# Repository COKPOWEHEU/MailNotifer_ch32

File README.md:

# MailNotifer_ch32
My version of Mail Notifer by RISO KAGAKU

The device that allows you to indicate something using an RGB LED. Also, unlike the prototype, an LCD screen has been added to display text information. Many features are now configured using files on a virtual "flash drive"

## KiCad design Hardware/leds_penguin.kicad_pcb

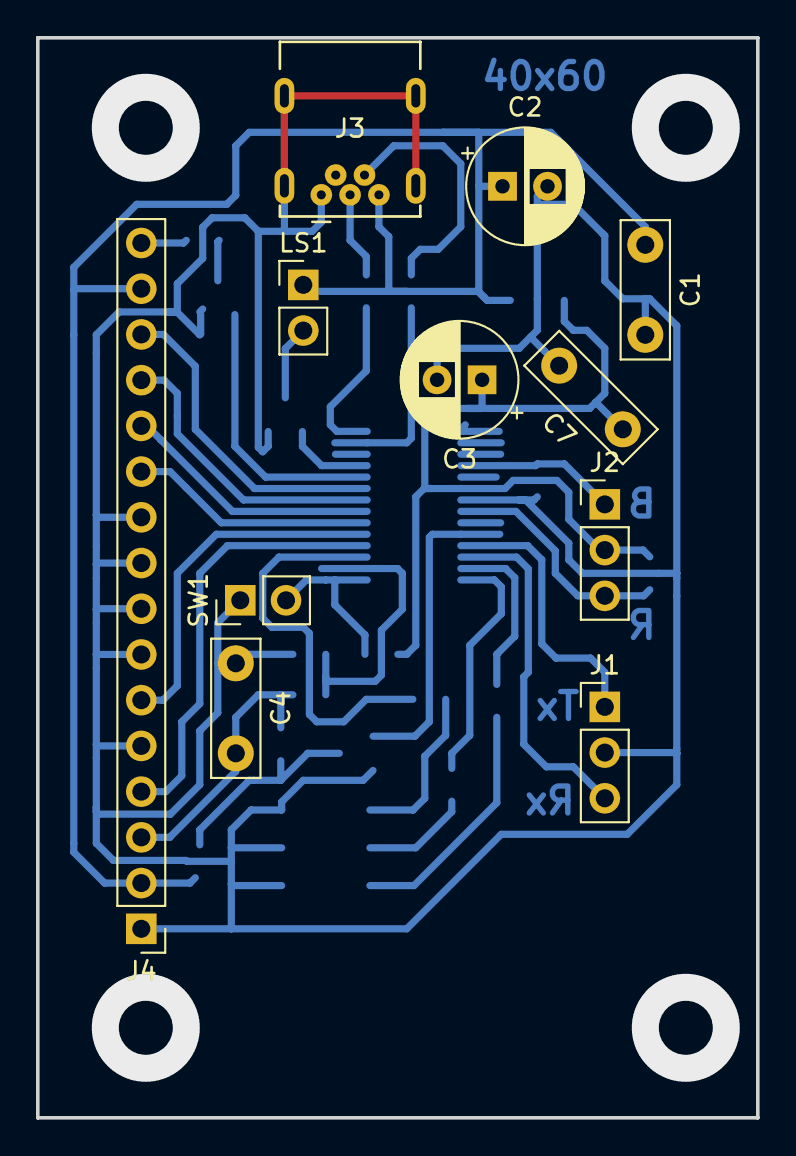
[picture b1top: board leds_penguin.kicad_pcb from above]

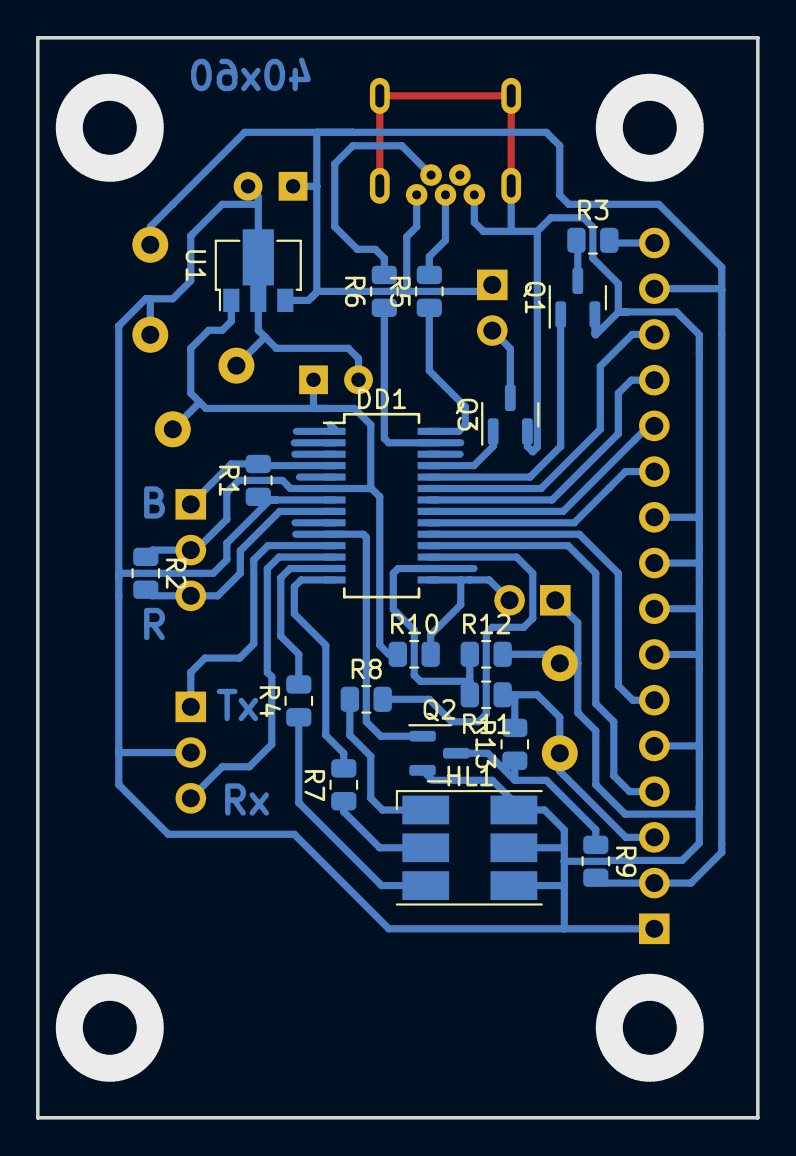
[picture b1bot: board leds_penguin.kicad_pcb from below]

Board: 2 copper layers, 40.0 x 60.0 mm, 30 parts (19 on the bottom side), 33 nets.

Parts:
C1, C4, C7: 1.0; C_Disc_D7.5mm_W2.5mm_P5.00mm
C2, C3: 47.0; CP_Radial_D6.3mm_P2.50mm
DD1: CH32V203G8; SSOP-28_3.9x9.9mm_P0.635mm
HL1: SMLVN6RGB; LED_RGB_Cree-PLCC-6_6x5mm_P2.1mm
J1: UART2; PinHeader_1x03_P2.54mm_Vertical
J2: BRST; PinHeader_1x03_P2.54mm_Vertical
J3: USBD; USB-mini
J4: Conn_01x16; PinHeader_1x16_P2.54mm_Vertical
LS1: Speaker; PinHeader_1x02_P2.54mm_Vertical
Q1, Q2, Q3: IRLML0030; SOT-23
R1, R2, R3, R4, R5, R6, R7, R8, R10, R11, R12: R; R_0805_2012Metric
R9: 1k; R_0805_2012Metric
R13: 10k; R_0805_2012Metric
SW1: SW_Omron_B3FS; PinHeader_1x02_P2.54mm_Vertical
U1: L78L33_SOT89; SOT-89-3

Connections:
+5V: C1.1, C2.1, J3.1 (VBUS), J4.2, J4.15, LS1.1, R9.2, U1.3 (IN)
/BLK: J4.16, R3.2
/D4: DD1.20 (PB1/PB12), J4.11
/D5: DD1.21 (PB13), J4.12
/D6: DD1.22 (PB14), J4.13
/D7: DD1.23 (PB15), J4.14
/E: DD1.19 (PB11), J4.6
/RS: DD1.18 (PB10), J4.4
/VO: C4.2, J4.3, R11.1, R13.2
GNDD: C1.2, C2.2, C3.2, C4.1, C7.2, DD1.7 (GND), HL1.4 (GK), HL1.5 (RK), HL1.6 (BK), J1.2, J3.5 (GND), J3.6 (Shield), J4.1, J4.5, J4.7, J4.8, J4.9, J4.10, Q1.2 (S), Q2.2 (S), Q3.2 (S), R1.1, R12.2, SW1.1, U1.2 (GND)
unnamed: DD1.4 (Boot0), J2.1, R1.2
unnamed: DD1.8 (NRST), J2.3, R2.2
unnamed: DD1.10 (PA1), Q2.1 (G)
unnamed: DD1.11 (PA2/TX2(B)), J1.1
unnamed: DD1.12 (PA3/RX2(B)), J1.3
unnamed: DD1.15 (PA4), R10.2, SW1.2
unnamed: DD1.16 (PA5), R11.2, R12.1
unnamed: DD1.13 (PA6), R4.2
unnamed: DD1.17 (PA7), R8.2
unnamed: DD1.24 (PA8), Q1.1 (G)
unnamed: DD1.25 (PA9), Q3.1 (G)
unnamed: DD1.27 (PA11/USBD_D-), R6.1
unnamed: DD1.28 (PA12/USBD_D+), R5.1
unnamed: DD1.14 (PB0), R7.2
unnamed: HL1.1 (BA), R8.1
unnamed: HL1.3 (GA), R4.1
unnamed: HL1.2 (RA), R7.1
unnamed: J3.3 (D+), R5.2
unnamed: J3.2 (D-), R6.2
unnamed: Q1.3 (D), R3.1
unnamed: Q2.3 (D), R9.1, R13.1
unnamed: LS1.2, Q3.3 (D)
VCC: C3.1, C7.1, DD1.6 (VCC), J2.2, R2.1, R10.1, U1.1 (OUT)

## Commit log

2025-06-07 Add hardware
2025-06-07 Add Firmware
2025-06-07 Add readme
2025-06-07 Fix flash name
2025-06-08 Add temporary 'flash example' file; Add udev rules
2025-06-09 Add single storage for saved data
2025-06-09 Add save / restore settings into flash
2025-06-10 eeflash: Add check if new data is equal with saved
2025-06-10 Fix auto reload user symbols to LCD
2025-06-13 Add peridically reinitialization of LCD
2025-06-15 lcd: add ESC-commands to control brightness; Fix \e[?J
